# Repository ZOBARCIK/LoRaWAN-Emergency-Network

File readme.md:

this branch is for the modules that are on hold, waiting for the project to advance

-crc16dnp

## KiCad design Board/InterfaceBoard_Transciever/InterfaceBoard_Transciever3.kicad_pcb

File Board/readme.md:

boards are done

1 gateway board for concentrator module, featuring a female sma connector and extra debug holes for esp32

3 transciever boards for different type of lora packets

//update

changed the footprints for 10uf caps for convinience. kart daha f/p olsun diye footprint değiştirdim amk. cebime 150 lira kaldı. also removed debug pinholes on the gateway card because somehow they lost their reference values, so script wouldnt autoroute them.
only transciever 3 is updated with the new footprint, since we willl only use that one.

--possible improvements
instead of through hole lora components, solder the chips directly onto board for production. also could find esp32 dev modules without presoldered pins and do the same

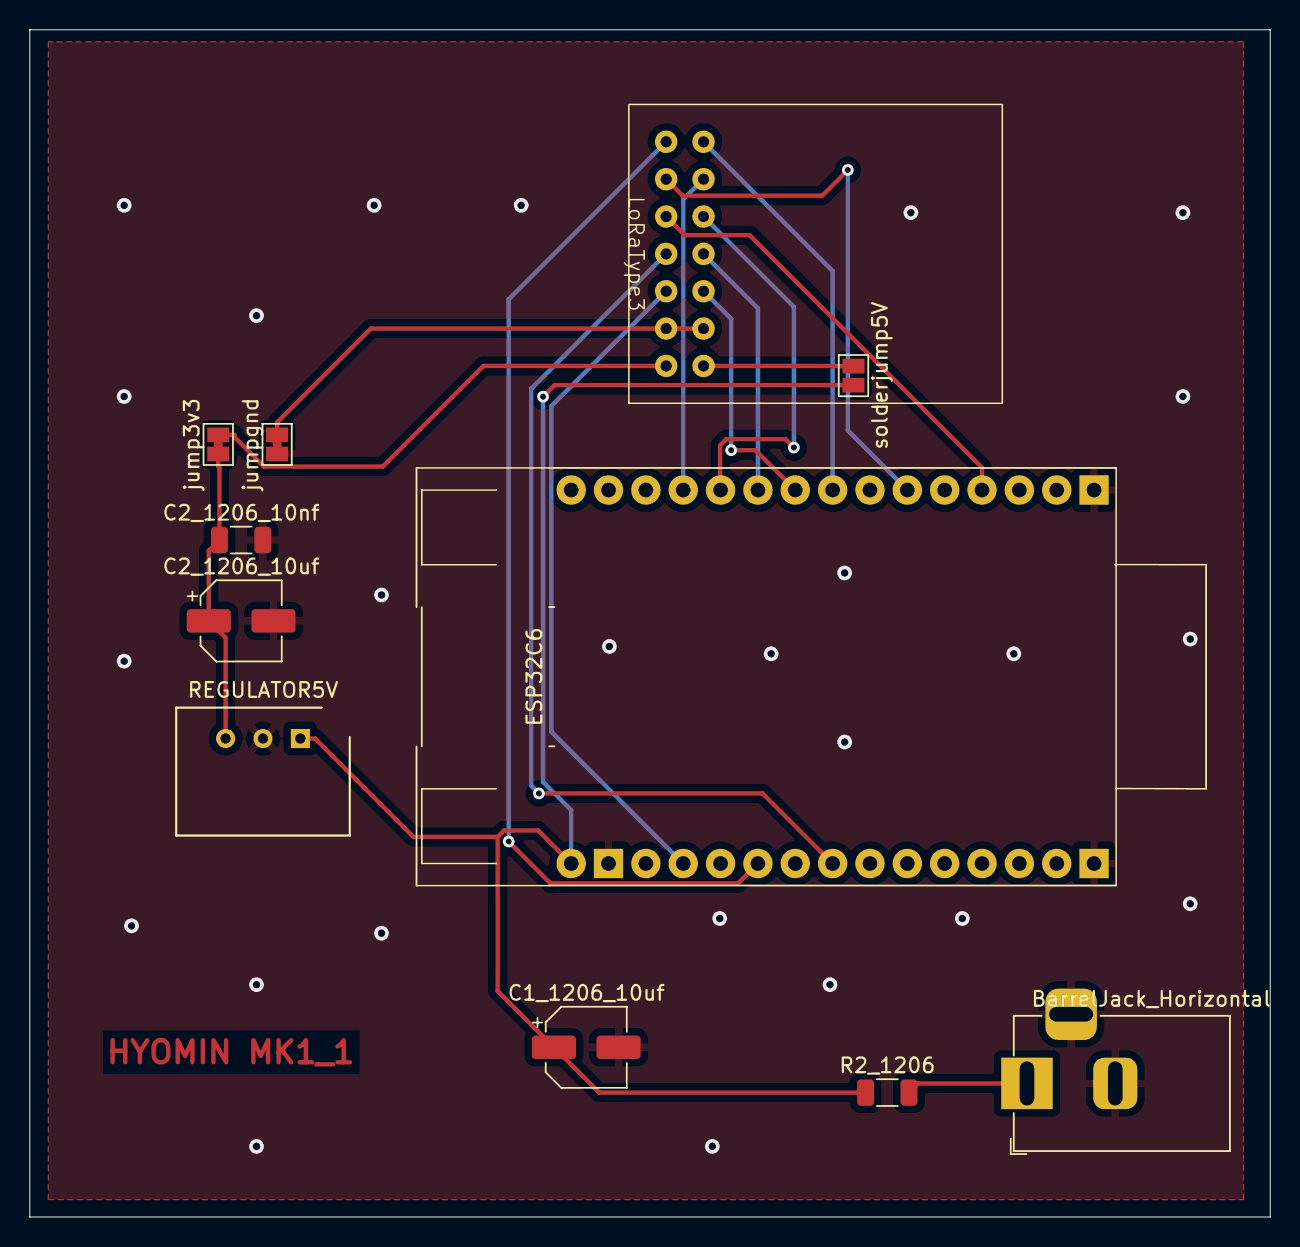
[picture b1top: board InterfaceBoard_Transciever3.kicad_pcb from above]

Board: 2 copper layers, 84.4 x 80.7 mm, 11 parts (0 on the bottom side), 17 nets.

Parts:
BarrelJack_Horizontal: BarrelJack_Horizontal
C1_1206_10uf: C1_1206_10uf; CP_Elec_5x3
C2_1206_10nf: C3_1206_100nf; C_1206_3216Metric
C2_1206_10uf: C2_1206_10uf; CP_Elec_5x3
ESP32C6: ESP32C6
LoRaType3: LoRaType3
R2_1206: R2_1206; C_1206_3216Metric
REGULATOR5V: SIP3_11.6x8.5mm
jump3v3: SolderJumper-2_P1.3mm_Bridged_Pad1.0x1.5mm
jumpgnd: SolderJumper-2_P1.3mm_Bridged_Pad1.0x1.5mm
solderjump5V: SolderJumper-2_P1.3mm_Open_Pad1.0x1.5mm

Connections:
3V3: C2_1206_10nf.1, C2_1206_10uf.1, REGULATOR5V.3, jump3v3.1
5V: C1_1206_10uf.1, ESP32C6.5V, R2_1206.1, REGULATOR5V.1, solderjump5V.2
5VEXT: BarrelJack_Horizontal.1, R2_1206.2
DI0: ESP32C6.11, LoRaType3.13
DI1: ESP32C6.10, LoRaType3.12
DI2: ESP32C6.8, LoRaType3.11
DI3: ESP32C6.1, LoRaType3.10
DI4: ESP32C6.0, LoRaType3.14
GND: BarrelJack_Horizontal.2, BarrelJack_Horizontal.3, C1_1206_10uf.2, C2_1206_10nf.2, C2_1206_10uf.2, ESP32C6.GND, REGULATOR5V.2, jumpgnd.1
L3V3: LoRaType3.7, jump3v3.2
L5V: LoRaType3.8, solderjump5V.1
LGND: LoRaType3.6, LoRaType3.9, jumpgnd.2
LMISO: ESP32C6.6, LoRaType3.2
LMOSI: ESP32C6.4, LoRaType3.3
LNSS: ESP32C6.22, LoRaType3.4
LRST: ESP32C6.18, LoRaType3.5
LSCK: ESP32C6.20, LoRaType3.1

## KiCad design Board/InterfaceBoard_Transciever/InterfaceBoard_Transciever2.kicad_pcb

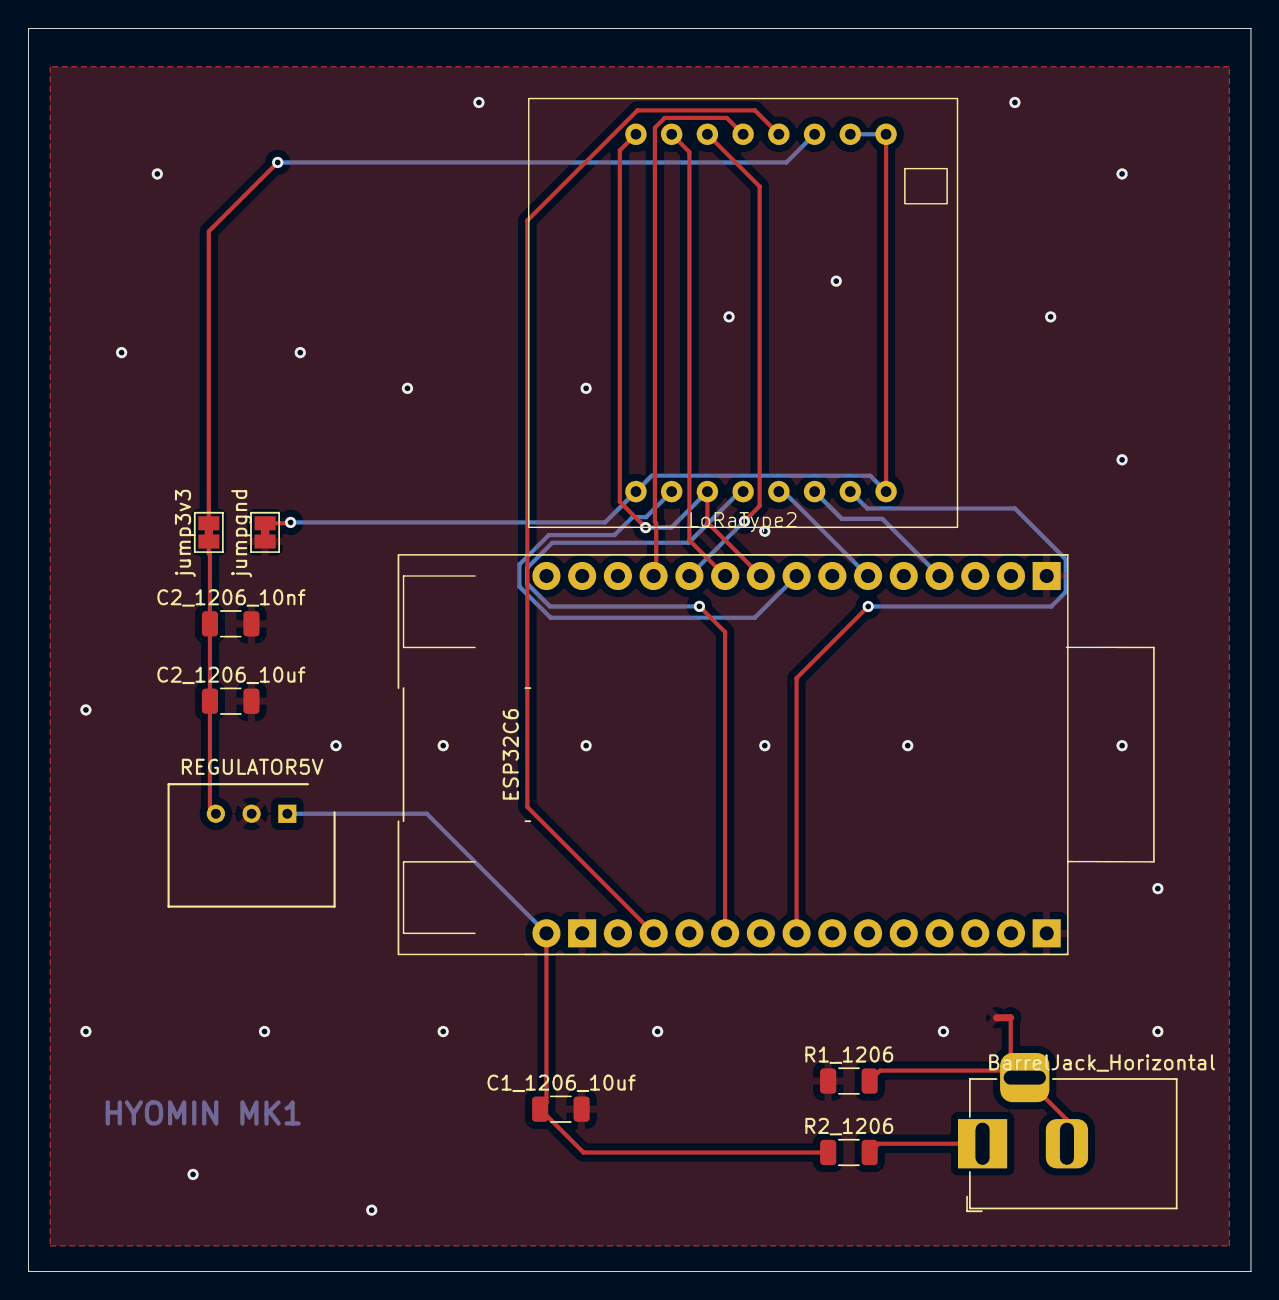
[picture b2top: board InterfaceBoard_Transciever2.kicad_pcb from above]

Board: 2 copper layers, 86.9 x 88.4 mm, 11 parts (0 on the bottom side), 17 nets.

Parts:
BarrelJack_Horizontal: BarrelJack_Horizontal
C1_1206_10uf: C1_1206_10uf; C_1206_3216Metric
C2_1206_10nf: C3_1206_100nf; C_1206_3216Metric
C2_1206_10uf: C2_1206_10uf; C_1206_3216Metric
ESP32C6: ESP32C6
LoRaType2: LoRaType2
R1_1206: R1_1206; C_1206_3216Metric
R2_1206: R2_1206; C_1206_3216Metric
REGULATOR5V: SIP3_11.6x8.5mm
jump3v3: SolderJumper-2_P1.3mm_Bridged_Pad1.0x1.5mm
jumpgnd: SolderJumper-2_P1.3mm_Bridged_Pad1.0x1.5mm

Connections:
3V3: C2_1206_10nf.1, C2_1206_10uf.1, REGULATOR5V.3, jump3v3.1
5V: C1_1206_10uf.1, ESP32C6.5V, R2_1206.1, REGULATOR5V.1
5VEXT: BarrelJack_Horizontal.1, R2_1206.2
DI0: ESP32C6.11, LoRaType2.13
DI1: ESP32C6.10, LoRaType2.14
DI2: ESP32C6.8, LoRaType2.15
DI3: ESP32C6.1, LoRaType2.3, LoRaType2.16
DI4: ESP32C6.0, LoRaType2.2
GND: C1_1206_10uf.2, C2_1206_10nf.2, C2_1206_10uf.2, ESP32C6.GND, R1_1206.1, REGULATOR5V.2, jumpgnd.1
GNDEXT: BarrelJack_Horizontal.2, BarrelJack_Horizontal.3, R1_1206.2
L3V3: LoRaType2.11, jump3v3.2
LGND: LoRaType2.1, LoRaType2.8, LoRaType2.9, LoRaType2.10, jumpgnd.2
LMISO: ESP32C6.6, LoRaType2.5
LMOSI: ESP32C6.4, LoRaType2.6
LNSS: ESP32C6.22, LoRaType2.7
LRST: ESP32C6.18, LoRaType2.12
LSCK: ESP32C6.20, LoRaType2.4

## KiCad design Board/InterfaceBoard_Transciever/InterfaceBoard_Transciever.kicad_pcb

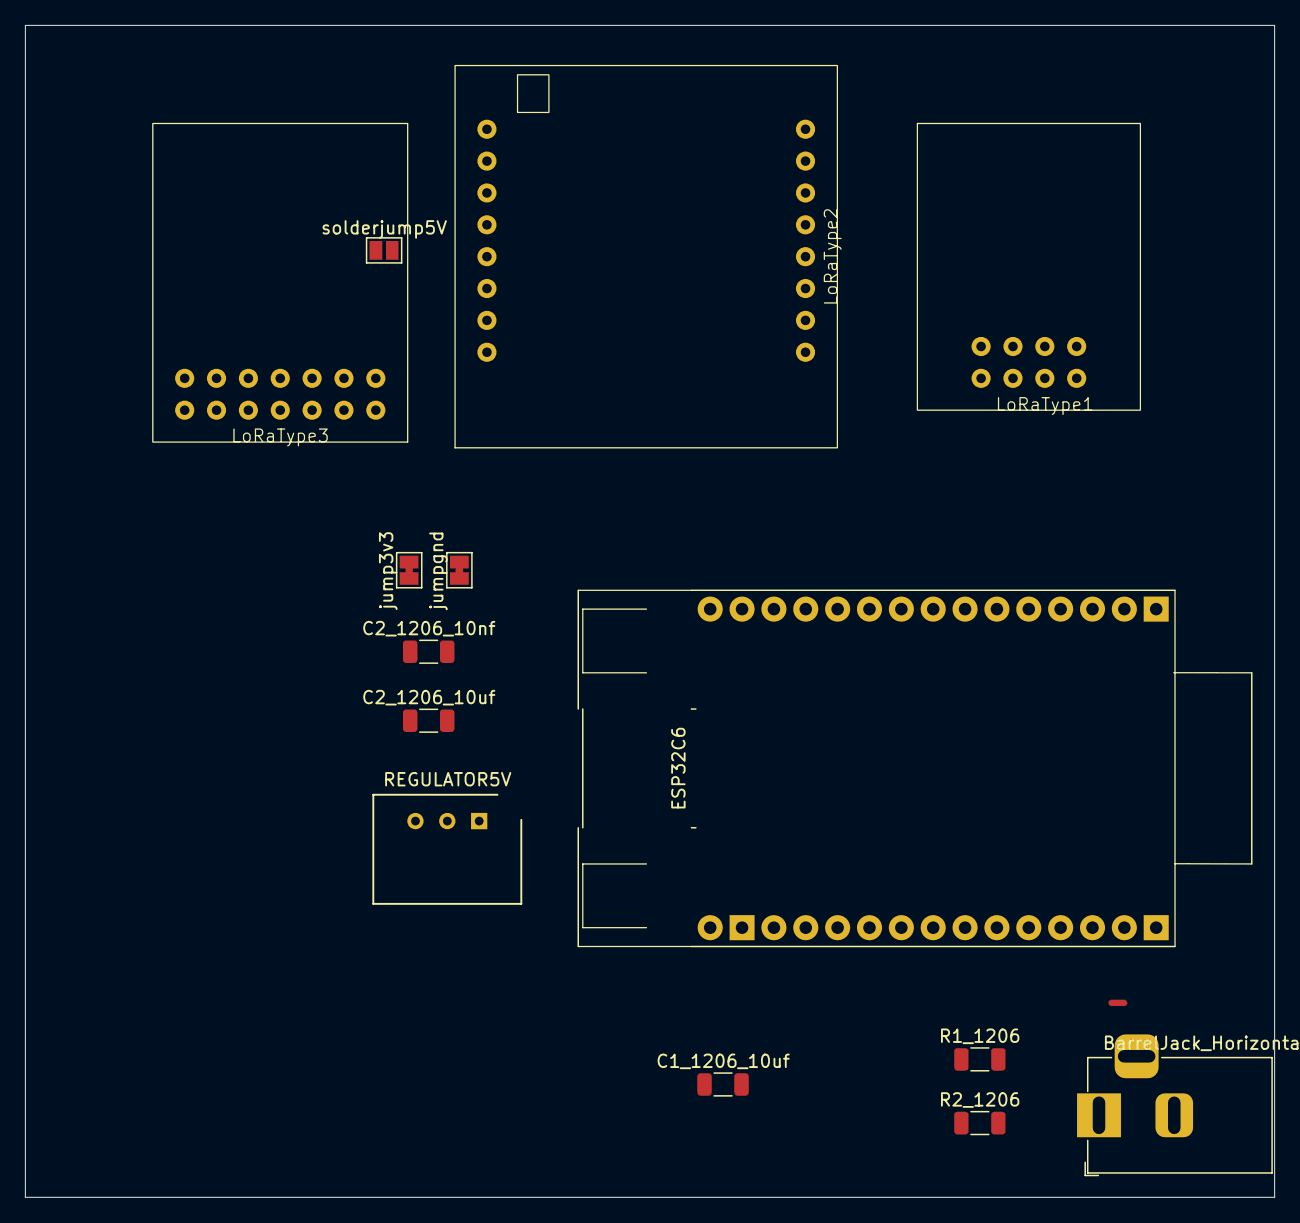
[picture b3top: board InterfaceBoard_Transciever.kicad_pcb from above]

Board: 2 copper layers, 99.6 x 93.4 mm, 14 parts (0 on the bottom side), 18 nets, no tracks yet.

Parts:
BarrelJack_Horizontal: BarrelJack_Horizontal
C1_1206_10uf: C1_1206_10uf; C_1206_3216Metric
C2_1206_10nf: C3_1206_100nf; C_1206_3216Metric
C2_1206_10uf: C2_1206_10uf; C_1206_3216Metric
ESP32C6: ESP32C6
LoRaType1: LoRaType1
LoRaType2: LoRaType2
LoRaType3: LoRaType3
R1_1206: R1_1206; C_1206_3216Metric
R2_1206: R2_1206; C_1206_3216Metric
REGULATOR5V: SIP3_11.6x8.5mm
jump3v3: SolderJumper-2_P1.3mm_Bridged_Pad1.0x1.5mm
jumpgnd: SolderJumper-2_P1.3mm_Bridged_Pad1.0x1.5mm
solderjump5V: SolderJumper-2_P1.3mm_Open_Pad1.0x1.5mm

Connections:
3V3: C2_1206_10nf.1, C2_1206_10uf.1, REGULATOR5V.3, jump3v3.1
5V: C1_1206_10uf.1, ESP32C6.5V, R2_1206.1, REGULATOR5V.1, solderjump5V.2
5VEXT: BarrelJack_Horizontal.1, R2_1206.2
DI0: ESP32C6.11, LoRaType1.1, LoRaType2.13, LoRaType3.13
DI1: ESP32C6.10, LoRaType2.14, LoRaType3.12
DI2: ESP32C6.8, LoRaType2.15, LoRaType3.11
DI3: ESP32C6.1, LoRaType2.3, LoRaType2.16, LoRaType3.10
DI4: ESP32C6.0, LoRaType2.2, LoRaType3.14
GND: C1_1206_10uf.2, C2_1206_10nf.2, C2_1206_10uf.2, ESP32C6.GND, R1_1206.1, REGULATOR5V.2, jumpgnd.1
GNDEXT: BarrelJack_Horizontal.2, BarrelJack_Horizontal.3, R1_1206.2
L3V3: LoRaType1.4, LoRaType2.11, LoRaType3.7, jump3v3.2
L5V: LoRaType3.8, solderjump5V.1
LGND: LoRaType1.8, LoRaType2.1, LoRaType2.8, LoRaType2.9, LoRaType2.10, LoRaType3.6, LoRaType3.9, jumpgnd.2
LMISO: ESP32C6.6, LoRaType1.5, LoRaType2.5, LoRaType3.2
LMOSI: ESP32C6.4, LoRaType1.2, LoRaType2.6, LoRaType3.3
LNSS: ESP32C6.22, LoRaType1.3, LoRaType2.7, LoRaType3.4
LRST: ESP32C6.18, LoRaType1.7, LoRaType2.12, LoRaType3.5
LSCK: ESP32C6.20, LoRaType1.6, LoRaType2.4, LoRaType3.1

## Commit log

2025-02-23 CENNETİN İLK KATINI YARATTIK
    AYRICA EUNJUNG
2025-02-25 basically 10 minute job done in 2 hours, not proud but fuck it, I like giving cigarette breaks anyways
2025-02-27 Hayırlısı olsun
2025-02-27 coding standarts for men
2025-03-16 its 6 in the morning ffs I need a cigarette
2025-03-22 wake up honey, new commit just dropped
2025-03-24 mpcie nets, gatewayboard ext pins and sma port have been added. almost done
2025-03-25 bu gece bitsin artık arda kaldır götünü amk
2025-03-26 vücudum uyu diyor ama sonsuz uykuya dalmayacaksam bir anlamı yok
2025-03-26 I commit this this update for all the broken hearts around the world
2025-03-29 kart daha f/p yapıldı artan parayla mamutta 2-3 bira içilir aga
2025-04-05 fixed the issue the label HYOMIN MK1_1 on the transciever being on the other side, such an important issue, literal fucking disaster if you ask me
2025-04-06 added gerber and drill files
2025-04-18 create node codebase
2025-04-18 add lora dependency, esp-idf-sx127x
2025-05-02 create lora packets
2025-05-04 COMMİTLEMEDEN PUSHLAMIŞIZ AMINAKKE
2025-05-08 refactor packets
2025-05-08 implement distant_vector algorithm
2025-05-08 include lora header
